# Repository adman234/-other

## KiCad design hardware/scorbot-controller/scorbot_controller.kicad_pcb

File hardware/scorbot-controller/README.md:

# Scorbot ER-4u ESP32 master board (KiCad)

KiCad project for the replacement controller: an ESP32 DevKit, six Pololu
DRV8874 carriers, a DROK mini 5 V buck module and two ADS1115 ADC
modules plug into a master board, and the robot's DD-50 cable plugs straight
into the board edge. The only SMD chip left for JLCPCB to place is the
TCA9555; everything else on the board is passives, LEDs and diodes.

**Status: v0.2, generated: schematic complete, PCB placed and autorouted (needs a human review before ordering).**

| File | What it is |
| --- | --- |
| `scorbot_controller.kicad_pro/.kicad_sch/.kicad_pcb` | The KiCad project (opens in KiCad 7, 8 or 9) |
| `lib/Scorbot.kicad_sym`, `lib/Scorbot.pretty/` | Custom parts: DevKit socket, DRV8874 carrier socket, DD-50 female R/A |
| `docs/schematic.pdf`, `docs/pcb_placement.png`, `docs/pcb_routed_F.png`, `docs/pcb_routed_B.png` | Previews (B side is mirrored) |
| `bom.csv` | Grouped BOM |
| `generator/design.py` | **Single source of truth**: every part, footprint, pin-to-net map and placement |
| `generate.sh` | Regenerates everything from `design.py`, then checks it |

## Regenerating

```sh
pip install kiutils cairosvg   # plus KiCad 7+ (kicad-cli and its pcbnew Python module)
# optional autorouting: Java 17+, xvfb-run and the Freerouting 1.9.0 jar
# (https://github.com/freerouting/freerouting/releases/tag/v1.9.0)
FREEROUTING_JAR=/path/freerouting-1.9.0.jar ./generate.sh
```

Routing takes about 3 minutes. `gen_route.py` retries up to `FREEROUTING_TRIES`
times (default 3) because Freerouting's result varies between runs, and it
keeps the run with the fewest unconnected items.

`generate.sh` writes the library, schematic, PCB and BOM, then:

- exports KiCad's own netlist from the schematic and checks it against
  `design.py` pin by pin (currently 354 connections, 0 mismatches);
- runs KiCad DRC on the board. Current result: 0 unconnected items, 0
  clearance or courtyard errors, and a few silkscreen and thermal-relief
  warnings. `lib_footprint_issues` only appears when the
  standard KiCad libraries aren't in the global library table.

Editing the `.kicad_sch` / `.kicad_pcb` by hand is fine once you take over
the design; just stop running the generator after that, or it overwrites your
changes.

## Must check before ordering boards

Blockers (the board is wrong or unbuildable until these are done):

1. **Pololu carrier pin order is a placeholder, and probably wrong.** The
   #4035 board is 0.6" x 0.7", which only fits 7 pins per side, but
   `CARRIER_ROWS` has 6 + 8. IMODE is most likely not broken out (the
   carrier pulls it to GND through 20 k), leaving 7 logic pins. Copy the
   real order and row spacing from Pololu's pinout drawing (or a carrier in
   hand) into `CARRIER_ROWS` / `CARRIER_ROW_SPACING`, then re-run
   `generate.sh`; it re-places and re-routes the board.
2. **DevKit row spacing.** `DEVKIT_ROW_SPACING = 25.4` mm. Measure your
   38-pin DevKitC between pin centres; clones vary.
3. **DD-50 footprint** is generated from KiCad's D-sub geometry (pitch
   2.77 x 2.84 mm, rows 1 and 3 aligned, D-shell hole spacing 61.11 mm).
   Print the board 1:1 and lay the connector on it, or check the drawing of
   the exact right-angle part you buy.
4. **JLC part numbers.** `fab/jlc_bom.csv` holds LCSC numbers from memory
   and search snapshots. Look each one up in JLCPCB's parts library (value,
   package, Basic vs Extended, stock) before ordering.

Check in KiCad / the JLC preview:

5. **Module pin orders**: the DROK buck socket (`BUCK_PINS`: IN+, IN-,
   OUT-, OUT+; the module's EN pin hangs off the end) and the ADS1115
   breakout (`ADS1115_PINS`, Adafruit #1085 order; other sellers differ).
6. **Autorouted copper.** Freerouting's result is DRC-clean but not pretty:
   long parallel runs across the middle, and motor/VM traces near the
   encoder lines. Look over the VM and MOT paths in particular.
7. **Copper weight.** VM carries up to the 5 A fuse current on 1.5 mm
   traces, and the motor outputs up to about 2.9 A (carrier limit) on
   0.8 mm. On 1 oz copper that is roughly a 20-25 C rise at those peaks.
   Order 2 oz copper, or widen VM/MOT in `netclasses.py` / `gen_route.py`.
8. **Part orientation in JLC's placement preview**: diode and LED
   polarity (D1, D3-D7) and pin 1 of U5. KiCad-to-JLC rotations sometimes
   need a 90/180 degree fix in `jlc_cpl.csv`.
9. **Screw terminal wire entry** (J2, J3, J7) should face the board edge.
   Check in KiCad's 3D viewer.
10. **Mechanical fit**: board is 185 x 128 mm with M3 holes in the
    corners; check the enclosure and that the DevKit's USB port and
    antenna end are reachable/clear.

## Ordering at JLCPCB

`generator/gen_fab.py` (run by `generate.sh`) writes `fab/`:

- `scorbot_controller_gerbers.zip`: upload as the PCB (2 layers, 1.6 mm,
  2 oz copper recommended).
- `jlc_bom.csv` and `jlc_cpl.csv`: upload for PCB Assembly, top side only.
  These list only the SMD parts JLC places. Everything else is
  hand-soldered: see the buy list in the plan doc.

## Design notes

- **DB50 pinout**: SCORBOT-ER 4u User Manual, Chapter 8 (identical to the
  ER III manual Table D-1). Pins 37-44 unused; pin 22 (gripper switch) has no
  connection in the arm. Motor +/- labels differ between manuals; firmware
  sets direction.
- **Encoders**: bare IR LEDs + phototransistors. 47 R per axis from 5 V for
  VLED (ER III reference value; check against the ER-4u's upgraded PC510
  encoders). P0/P1 have 4.7 k pull-ups to 3.3 V and 1 nF, straight into the
  ESP32 (no buffer); the PCNT glitch filter handles noise.
- **Power input, two options**: barrel jack J1 or screw terminal J2 (same
  nets; use one).
- **Fuse, two options**: fit EITHER the on-board mini blade holder F1
  (Keystone 3568, 5 A ATM fuse) OR the screw terminal J7 with an inline
  fuse holder wired across it. They are in parallel: two fuses in at once
  double the trip current, and a bare wire in J7 bypasses F1.
- **No reverse-polarity FET**: a reversed supply forward-biases the
  unidirectional SMBJ18A and blows the fuse.
- **E-stop**: no relay; the NC contacts sit in the VM line (J3), so they must
  be rated for total motor current. Logic stays powered.
- **Carrier current limit**: VREF is pulled to SLEEP (3.3 V) by 10 k on the
  carrier and CS has 2.49 k, giving about 2.9 A. R21-R26 (DNP) lower it.
- **Current sense**: two ADS1115 modules (0x48: CS1-4, 0x49: CS5, CS6 and
  VM/5.7). CS reads 1.12 V/A; use the ADS1115's +/-4.096 V range.
- Plan, firmware architecture and API: see the "Scorbot ER-4u ESP32
  Controller Plan" doc.

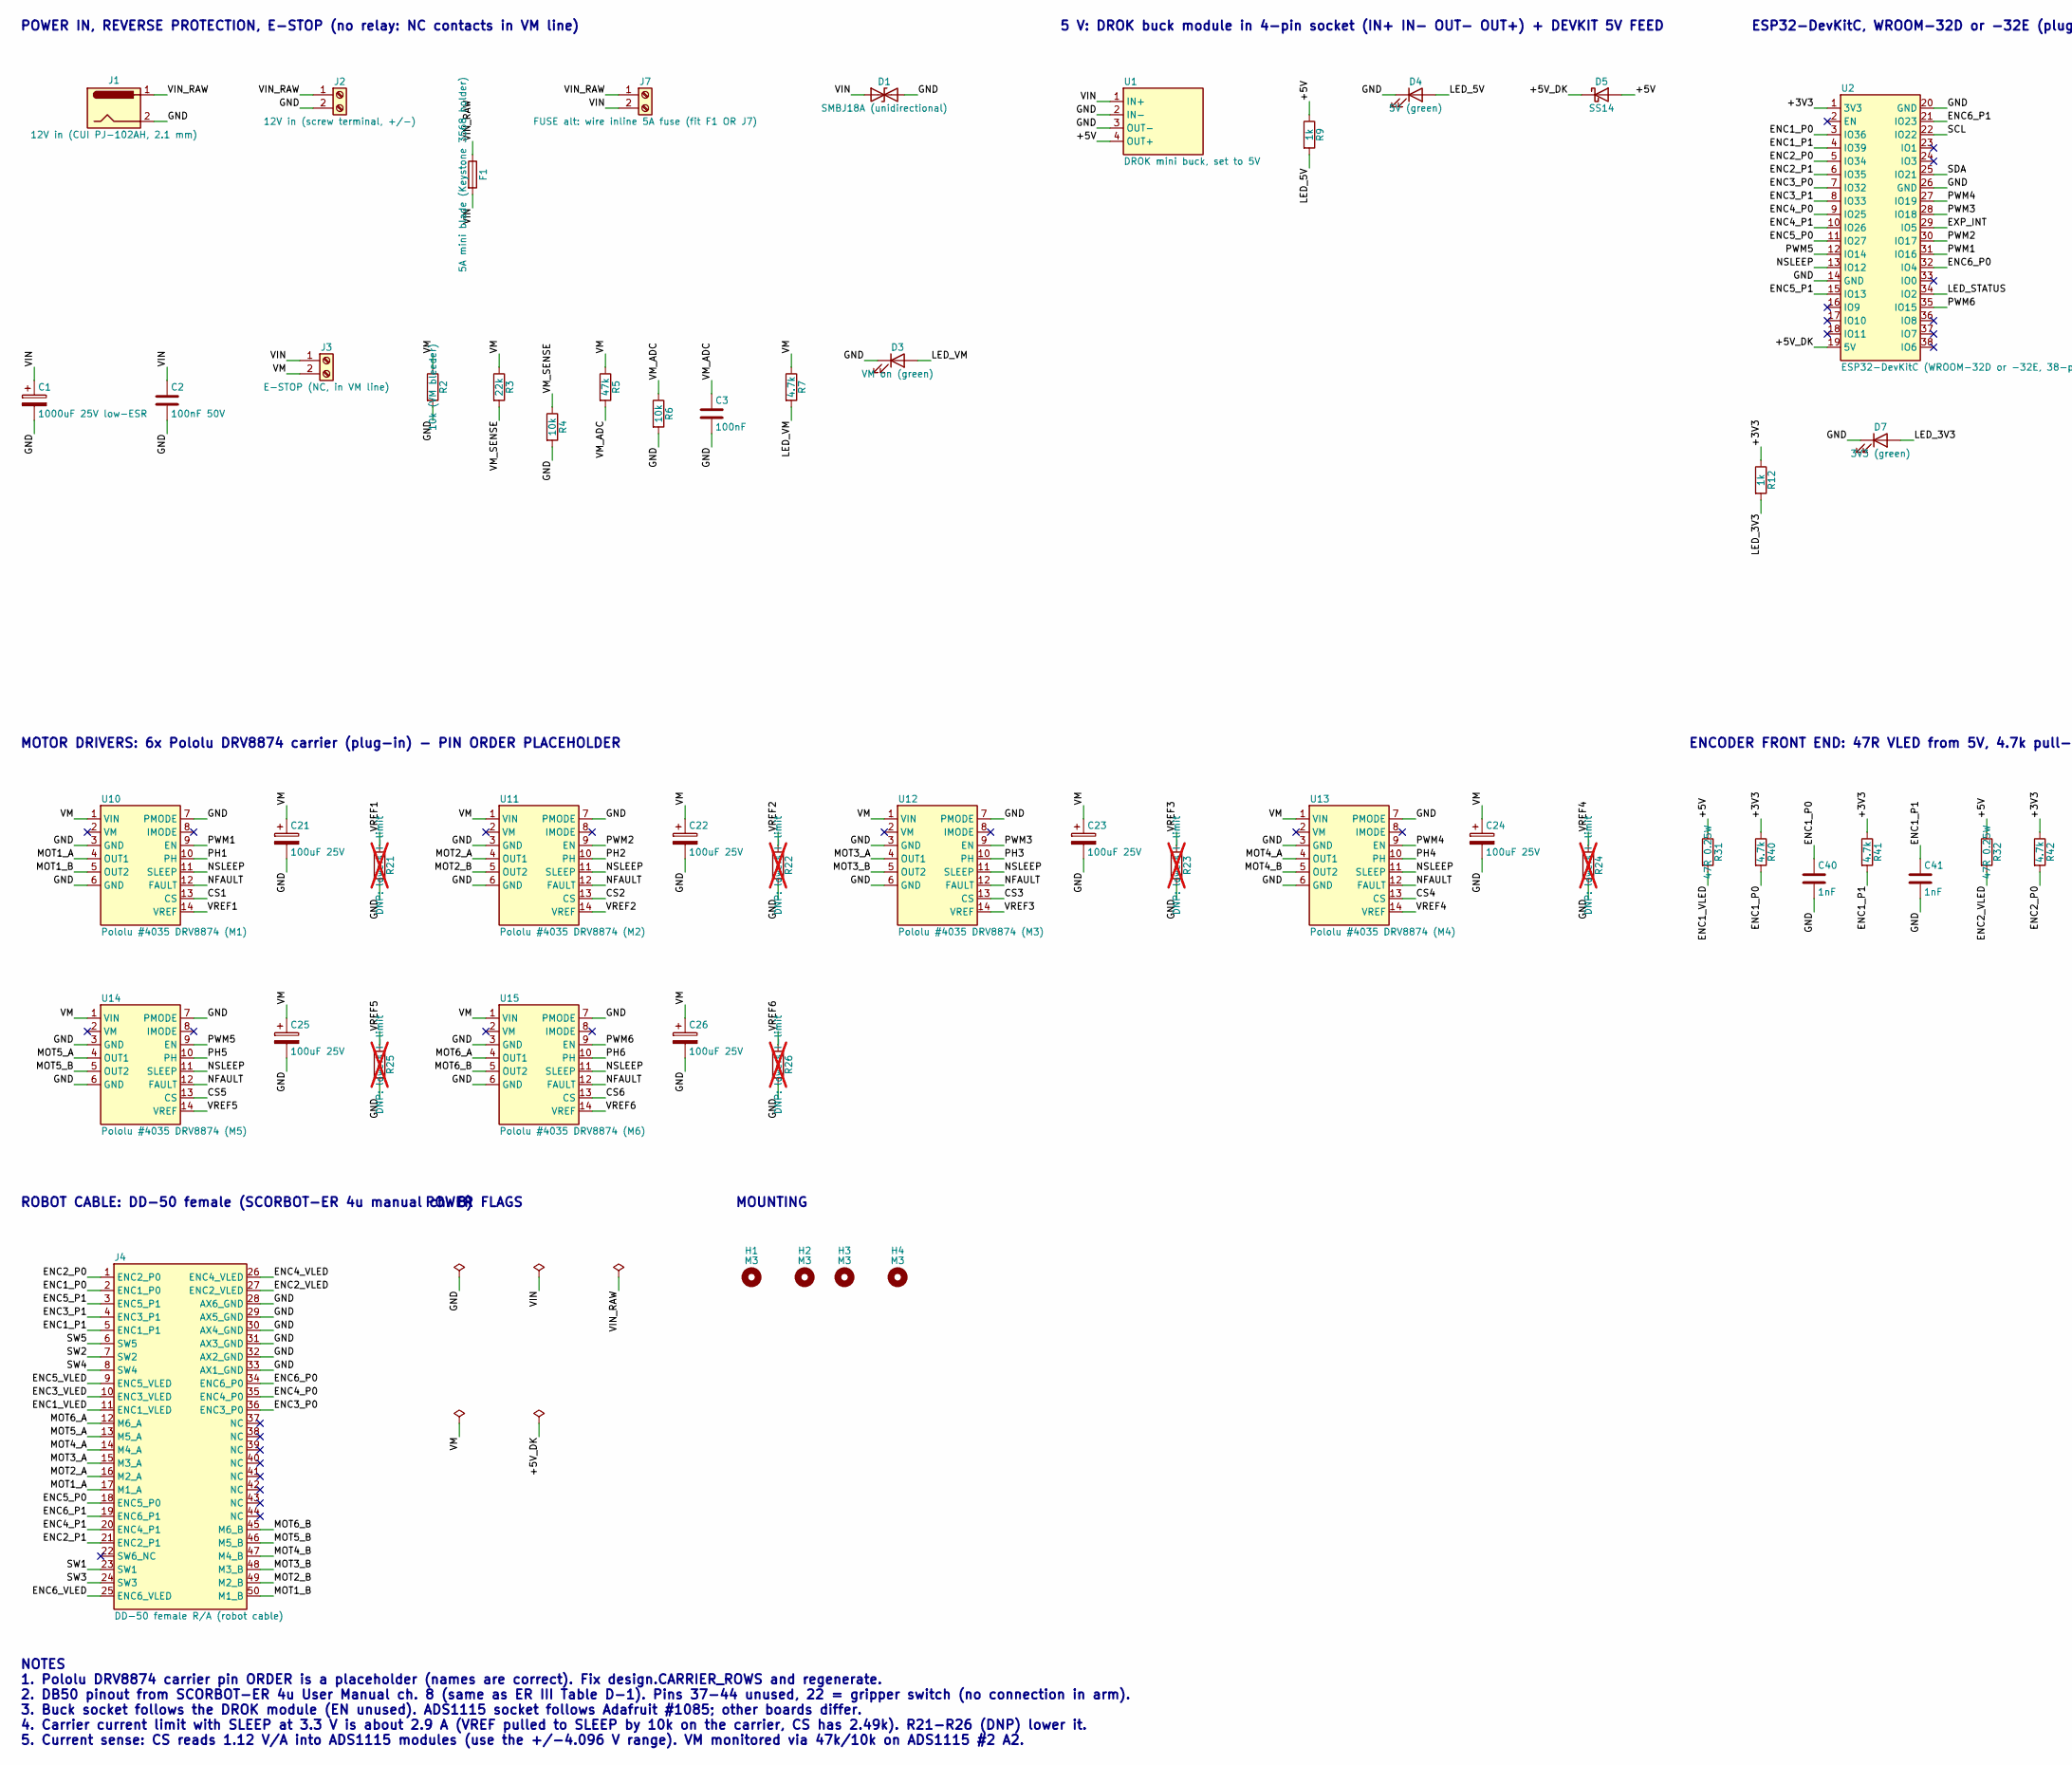
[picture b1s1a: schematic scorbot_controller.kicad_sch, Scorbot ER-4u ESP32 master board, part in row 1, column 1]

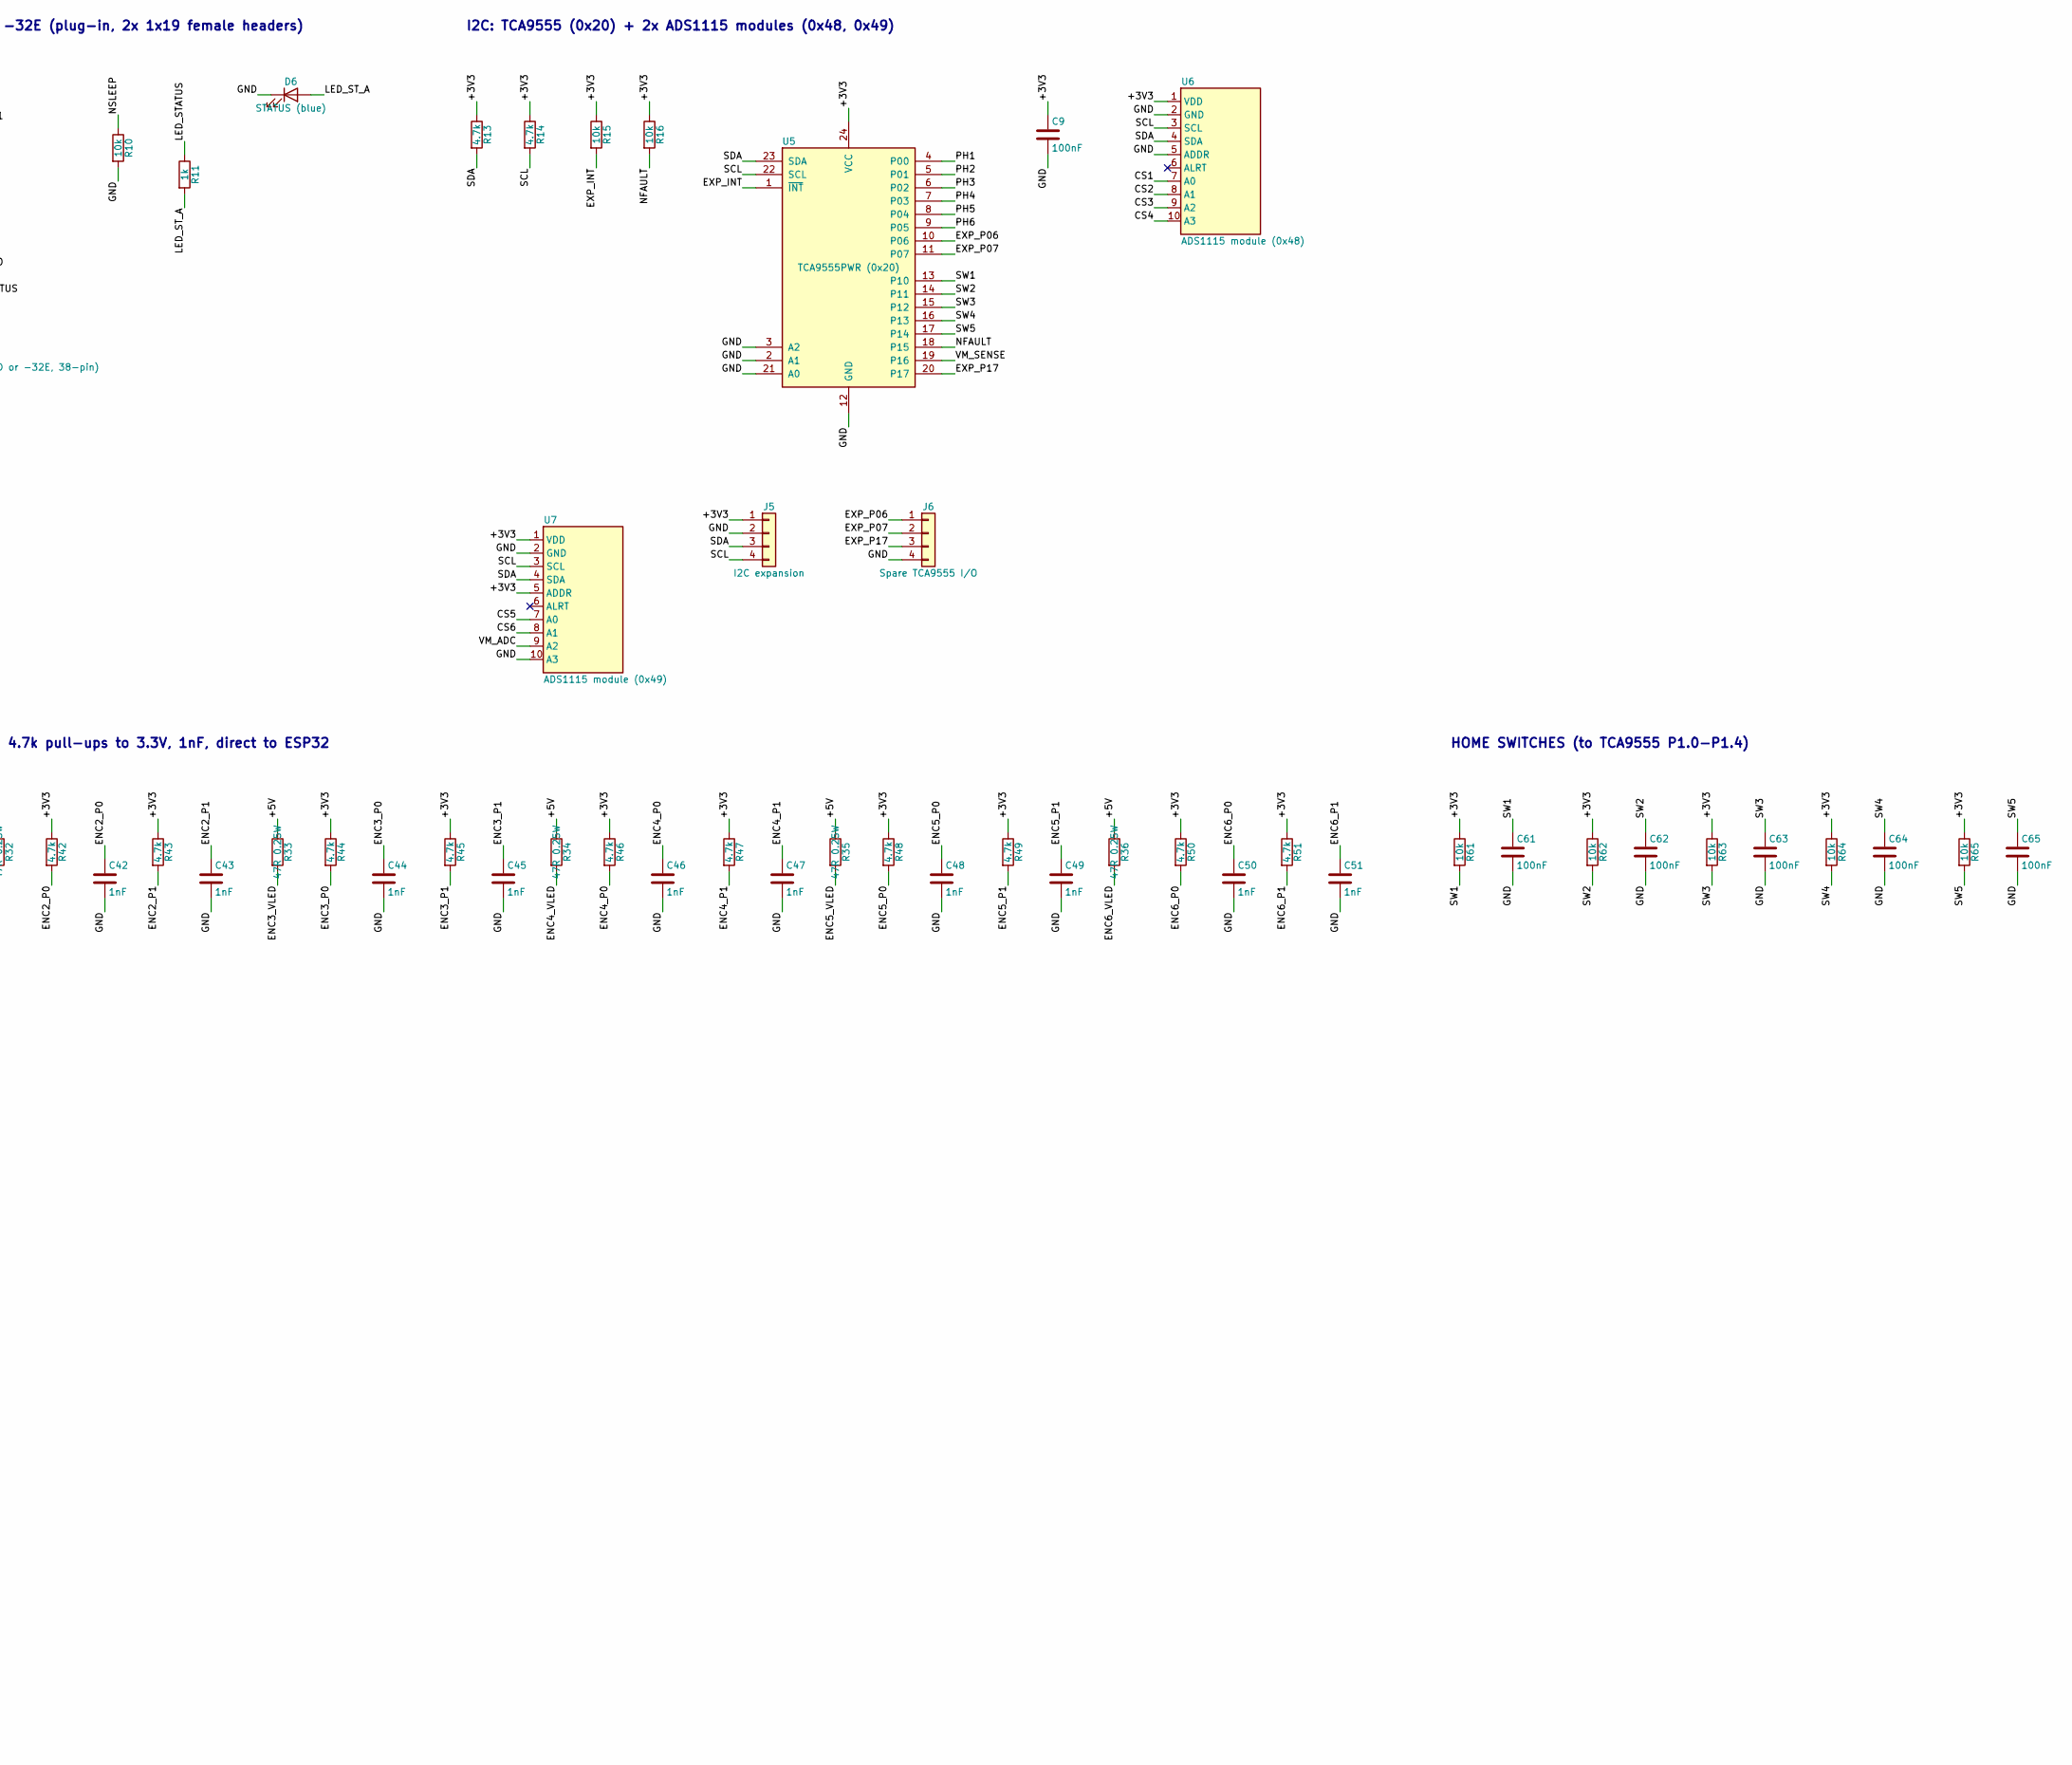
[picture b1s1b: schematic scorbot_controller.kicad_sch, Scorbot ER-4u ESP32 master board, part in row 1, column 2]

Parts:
C1: 1000uF 25V low-ESR; CP_Radial_D10.0mm_P5.00mm
C2: 100nF 50V; C_0805_2012Metric
C3, C9, C61, C62, C63, C64, C65: 100nF; C_0805_2012Metric
C21, C22, C23, C24, C25, C26: 100uF 25V; CP_Radial_D6.3mm_P2.50mm
C40, C41, C42, C43, C44, C45, C46, C47, C48, C49, C50, C51: 1nF; C_0805_2012Metric
D1: SMBJ18A (unidirectional); D_SMB
D3: VM on (green); LED_0805_2012Metric
D4: 5V (green); LED_0805_2012Metric
D5: SS14; D_SMA
D6: STATUS (blue); LED_0805_2012Metric
D7: 3V3 (green); LED_0805_2012Metric
F1: 5A mini blade (Keystone 3568 holder); Fuseholder_Blade_Mini_Keystone_3568
H1, H2, H3, H4: M3; MountingHole_3.2mm_M3
J1: 12V in (CUI PJ-102AH, 2.1 mm); BarrelJack_CUI_PJ-102AH_Horizontal
J2: 12V in (screw terminal, +/-); TerminalBlock_Phoenix_MKDS-1,5-2-5.08_1x02_P5.08mm_Horizont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
J3: E-STOP (NC, in VM line); TerminalBlock_Phoenix_MKDS-1,5-2-5.08_1x02_P5.08mm_Horizont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
J4: DD-50 female R/A (robot cable); DD50_Female_Horizontal_P2.77x2.84mm
J5: I2C expansion; PinHeader_1x04_P2.54mm_Vertical
J6: Spare TCA9555 I/O; PinHeader_1x04_P2.54mm_Vertical
J7: FUSE alt: wire inline 5A fuse (fit F1 OR J7); TerminalBlock_Phoenix_MKDS-1,5-2-5.08_1x02_P5.08mm_Horizont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
R2: 10k (VM bleeder); R_1206_3216Metric
R3: 22k; R_0805_2012Metric
R4, R6, R10, R15, R16, R61, R62, R63, R64, R65: 10k; R_0805_2012Metric
R5: 47k; R_0805_2012Metric
R7, R13, R14, R40, R41, R42, R43, R44, R45, R46, R47, R48, R49, R50, R51: 4.7k; R_0805_2012Metric
R9, R11, R12: 1k; R_0805_2012Metric
R21, R22, R23, R24, R25, R26: DNP: lowers I-limit; R_0805_2012Metric; not fitted
R31, R32, R33, R34, R35, R36: 47R 0.25W; R_1206_3216Metric
U1: DROK mini buck, set to 5V; Buck_Module_4pin_Socket
U2: ESP32-DevKitC (WROOM-32D or -32E, 38-pin); ESP32_DevKitC_V4_Socket
U5: TCA9555PWR (0x20); TSSOP-24_4.4x7.8mm_P0.65mm
U6: ADS1115 module (0x48); ADS1115_Module_Socket
U7: ADS1115 module (0x49); ADS1115_Module_Socket
U10: Pololu #4035 DRV8874 (M1); Pololu_DRV8874_Carrier_Socket
U11: Pololu #4035 DRV8874 (M2); Pololu_DRV8874_Carrier_Socket
U12: Pololu #4035 DRV8874 (M3); Pololu_DRV8874_Carrier_Socket
U13: Pololu #4035 DRV8874 (M4); Pololu_DRV8874_Carrier_Socket
U14: Pololu #4035 DRV8874 (M5); Pololu_DRV8874_Carrier_Socket
U15: Pololu #4035 DRV8874 (M6); Pololu_DRV8874_Carrier_Socket

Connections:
+3V3: C9.1, J5.1, R12.1, R13.1, R14.1, R15.1, R16.1, R40.1, R41.1, R42.1, R43.1, R44.1, R45.1, R46.1, R47.1, R48.1, R49.1, R50.1, R51.1, R61.1, R62.1, R63.1, R64.1, R65.1, U2.1 (3V3), U5.24 (VCC), U6.1 (VDD), U7.1 (VDD), U7.5 (ADDR)
+5V: D5.2 (A), R9.1, R31.1, R32.1, R33.1, R34.1, R35.1, R36.1, U1.4 (OUT+)
+5V_DK: D5.1 (K), U2.19 (5V)
CS1: U6.7 (A0), U10.13 (CS)
CS2: U6.8 (A1), U11.13 (CS)
CS3: U6.9 (A2), U12.13 (CS)
CS4: U6.10 (A3), U13.13 (CS)
CS5: U7.7 (A0), U14.13 (CS)
CS6: U7.8 (A1), U15.13 (CS)
ENC1_P0: C40.1, J4.2 (ENC1_P0), R40.2, U2.3 (IO36)
ENC1_P1: C41.1, J4.5 (ENC1_P1), R41.2, U2.4 (IO39)
ENC1_VLED: J4.11 (ENC1_VLED), R31.2
ENC2_P0: C42.1, J4.1 (ENC2_P0), R42.2, U2.5 (IO34)
ENC2_P1: C43.1, J4.21 (ENC2_P1), R43.2, U2.6 (IO35)
ENC2_VLED: J4.27 (ENC2_VLED), R32.2
ENC3_P0: C44.1, J4.36 (ENC3_P0), R44.2, U2.7 (IO32)
ENC3_P1: C45.1, J4.4 (ENC3_P1), R45.2, U2.8 (IO33)
ENC3_VLED: J4.10 (ENC3_VLED), R33.2
ENC4_P0: C46.1, J4.35 (ENC4_P0), R46.2, U2.9 (IO25)
ENC4_P1: C47.1, J4.20 (ENC4_P1), R47.2, U2.10 (IO26)
ENC4_VLED: J4.26 (ENC4_VLED), R34.2
ENC5_P0: C48.1, J4.18 (ENC5_P0), R48.2, U2.11 (IO27)
ENC5_P1: C49.1, J4.3 (ENC5_P1), R49.2, U2.15 (IO13)
ENC5_VLED: J4.9 (ENC5_VLED), R35.2
ENC6_P0: C50.1, J4.34 (ENC6_P0), R50.2, U2.32 (IO4)
ENC6_P1: C51.1, J4.19 (ENC6_P1), R51.2, U2.21 (IO23)
ENC6_VLED: J4.25 (ENC6_VLED), R36.2
EXP_INT: R15.2, U2.29 (IO5), U5.1 (~INT)
EXP_P06: J6.1, U5.10 (P06)
EXP_P07: J6.2, U5.11 (P07)
EXP_P17: J6.3, U5.20 (P17)
GND: C1.2, C2.2, C3.2, C9.2, C21.2, C22.2, C23.2, C24.2, C25.2, C26.2, C40.2, C41.2, C42.2, C43.2, C44.2, C45.2, C46.2, C47.2, C48.2, C49.2, C50.2, C51.2, C61.2, C62.2, C63.2, C64.2, C65.2, D1.2 (A2), D3.1 (K), D4.1 (K), D6.1 (K), D7.1 (K), J1.2, J2.2, J4.28 (AX6_GND), J4.29 (AX5_GND), J4.30 (AX4_GND), J4.31 (AX3_GND), J4.32 (AX2_GND), J4.33 (AX1_GND), J5.2, J6.4, R2.2, R4.2, R6.2, R10.2, R21.2, R22.2, R23.2, R24.2, R25.2, R26.2, U1.2 (IN-), U1.3 (OUT-), U2.14 (GND), U2.20 (GND), U2.26 (GND), U5.2 (A1), U5.3 (A2), U5.12 (GND), U5.21 (A0), U6.2 (GND), U6.5 (ADDR), U7.2 (GND), U7.10 (A3), U10.3 (GND), U10.6 (GND), U10.7 (PMODE), U11.3 (GND), U11.6 (GND), U11.7 (PMODE), U12.3 (GND), U12.6 (GND), U12.7 (PMODE), U13.3 (GND), U13.6 (GND), U13.7 (PMODE), U14.3 (GND), U14.6 (GND), U14.7 (PMODE), U15.3 (GND), U15.6 (GND), U15.7 (PMODE)
LED_3V3: D7.2 (A), R12.2
LED_5V: D4.2 (A), R9.2
LED_STATUS: R11.1, U2.34 (IO2)
LED_ST_A: D6.2 (A), R11.2
LED_VM: D3.2 (A), R7.2
MOT1_A: J4.17 (M1_A), U10.4 (OUT1)
MOT1_B: J4.50 (M1_B), U10.5 (OUT2)
MOT2_A: J4.16 (M2_A), U11.4 (OUT1)
MOT2_B: J4.49 (M2_B), U11.5 (OUT2)
MOT3_A: J4.15 (M3_A), U12.4 (OUT1)
MOT3_B: J4.48 (M3_B), U12.5 (OUT2)
MOT4_A: J4.14 (M4_A), U13.4 (OUT1)
MOT4_B: J4.47 (M4_B), U13.5 (OUT2)
MOT5_A: J4.13 (M5_A), U14.4 (OUT1)
MOT5_B: J4.46 (M5_B), U14.5 (OUT2)
MOT6_A: J4.12 (M6_A), U15.4 (OUT1)
MOT6_B: J4.45 (M6_B), U15.5 (OUT2)
NFAULT: R16.2, U5.18 (P15), U10.12 (FAULT), U11.12 (FAULT), U12.12 (FAULT), U13.12 (FAULT), U14.12 (FAULT), U15.12 (FAULT)
NSLEEP: R10.1, U2.13 (IO12), U10.11 (SLEEP), U11.11 (SLEEP), U12.11 (SLEEP), U13.11 (SLEEP), U14.11 (SLEEP), U15.11 (SLEEP)
PH1: U5.4 (P00), U10.10 (PH)
PH2: U5.5 (P01), U11.10 (PH)
PH3: U5.6 (P02), U12.10 (PH)
PH4: U5.7 (P03), U13.10 (PH)
PH5: U5.8 (P04), U14.10 (PH)
PH6: U5.9 (P05), U15.10 (PH)
PWM1: U2.31 (IO16), U10.9 (EN)
PWM2: U2.30 (IO17), U11.9 (EN)
PWM3: U2.28 (IO18), U12.9 (EN)
PWM4: U2.27 (IO19), U13.9 (EN)
PWM5: U2.12 (IO14), U14.9 (EN)
PWM6: U2.35 (IO15), U15.9 (EN)
SCL: J5.4, R14.2, U2.22 (IO22), U5.22 (SCL), U6.3 (SCL), U7.3 (SCL)
SDA: J5.3, R13.2, U2.25 (IO21), U5.23 (SDA), U6.4 (SDA), U7.4 (SDA)
SW1: C61.1, J4.23 (SW1), R61.2, U5.13 (P10)
SW2: C62.1, J4.7 (SW2), R62.2, U5.14 (P11)
SW3: C63.1, J4.24 (SW3), R63.2, U5.15 (P12)
SW4: C64.1, J4.8 (SW4), R64.2, U5.16 (P13)
SW5: C65.1, J4.6 (SW5), R65.2, U5.17 (P14)
VIN: C1.1, C2.1, D1.1 (A1), F1.2, J3.1, J7.2, U1.1 (IN+)
VIN_RAW: F1.1, J1.1, J2.1, J7.1
VM: C21.1, C22.1, C23.1, C24.1, C25.1, C26.1, J3.2, R2.1, R3.1, R5.1, R7.1, U10.1 (VIN), U11.1 (VIN), U12.1 (VIN), U13.1 (VIN), U14.1 (VIN), U15.1 (VIN)
VM_ADC: C3.1, R5.2, R6.1, U7.9 (A2)
VM_SENSE: R3.2, R4.1, U5.19 (P16)
VREF1: R21.1, U10.14 (VREF)
VREF2: R22.1, U11.14 (VREF)
VREF3: R23.1, U12.14 (VREF)
VREF4: R24.1, U13.14 (VREF)
VREF5: R25.1, U14.14 (VREF)
VREF6: R26.1, U15.14 (VREF)

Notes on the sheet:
POWER IN, REVERSE PROTECTION, E-STOP (no relay: NC contacts in VM line)
5 V: DROK buck module in 4-pin socket (IN+ IN- OUT- OUT+) + DEVKIT 5V FEED
ESP32-DevKitC, WROOM-32D or -32E (plug-in, 2x 1x19 female headers)
I2C: TCA9555 (0x20) + 2x ADS1115 modules (0x48, 0x49)
MOTOR DRIVERS: 6x Pololu DRV8874 carrier (plug-in) - PIN ORDER PLACEHOLDER
ENCODER FRONT END: 47R VLED from 5V, 4.7k pull-ups to 3.3V, 1nF, direct to ESP32
HOME SWITCHES (to TCA9555 P1.0-P1.4)
ROBOT CABLE: DD-50 female (SCORBOT-ER 4u manual ch. 8)
POWER FLAGS
MOUNTING
NOTES 1. Pololu DRV8874 carrier pin ORDER is a placeholder (names are correct). Fix design.CARRIER_ROWS and regenerate. 2. DB50 pinout from SCORBOT-ER 4u User Manual ch. 8 (same as ER III Table D-1). Pins 37-44 unused, 22 = gripper switch (no connection in arm). 3. Buck socket follows the DROK modu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

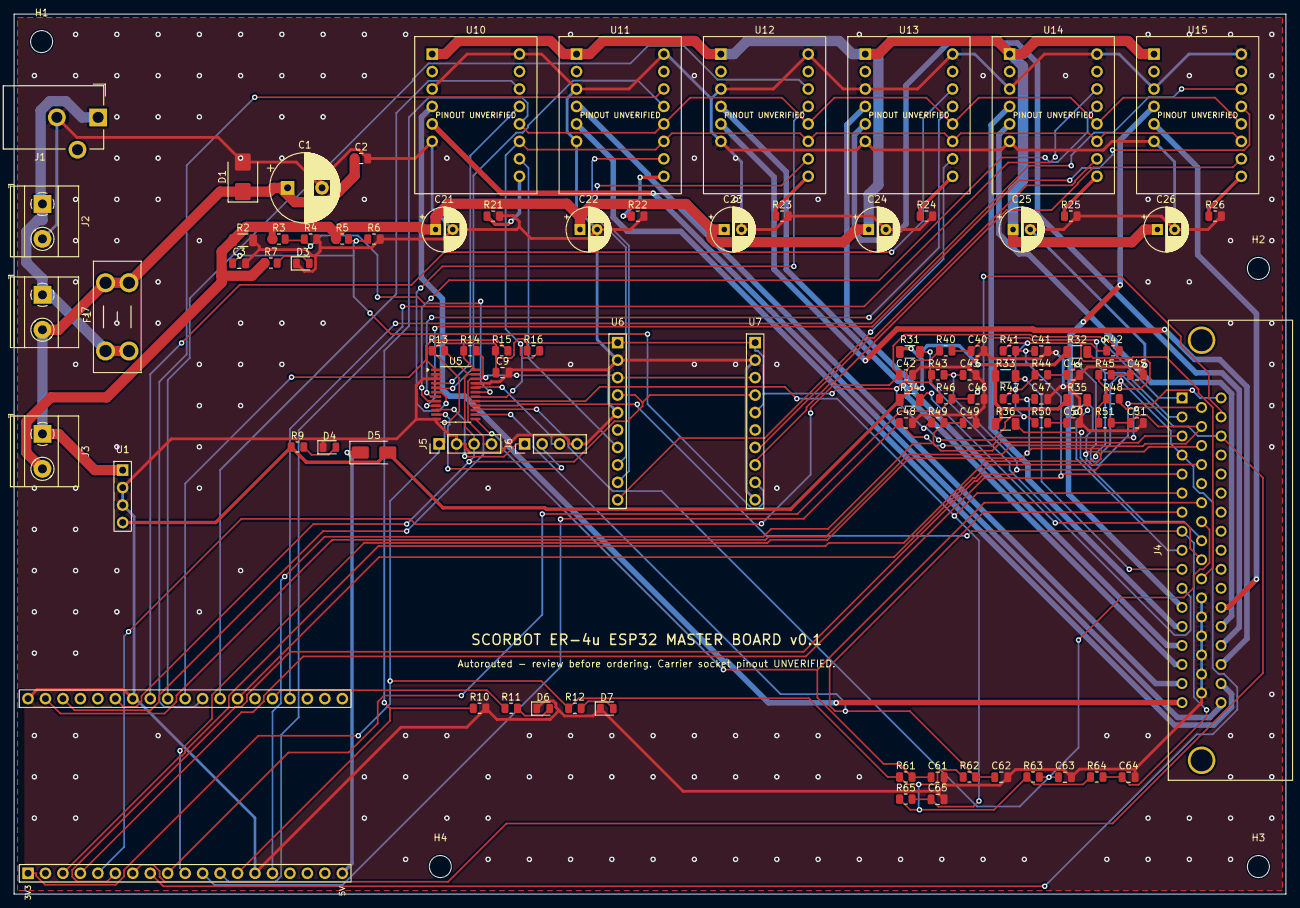
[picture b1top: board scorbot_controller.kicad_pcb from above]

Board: 2 copper layers, 185.0 x 128.0 mm, 99 parts (0 on the bottom side), 81 nets.

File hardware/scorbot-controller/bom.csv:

Qty,Value,Footprint,References,Populate
1,"12V in (CUI PJ-102AH, 2.1 mm)",Connector_BarrelJack:BarrelJack_CUI_PJ-102AH_Horizontal,J1,yes
1,"12V in (screw terminal, +/-)","TerminalBlock_Phoenix:TerminalBlock_Phoenix_MKDS-1,5-2-5.08_1x02_P5.08mm_Horizontal",J2,yes
1,5A mini blade (Keystone 3568 holder),Fuse:Fuseholder_Blade_Mini_Keystone_3568,F1,yes
1,FUSE alt: wire inline 5A fuse (fit F1 OR J7),"TerminalBlock_Phoenix:TerminalBlock_Phoenix_MKDS-1,5-2-5.08_1x02_P5.08mm_Horizontal",J7,yes
1,SMBJ18A (unidirectional),Diode_SMD:D_SMB,D1,yes
1,1000uF 25V low-ESR,Capacitor_THT:CP_Radial_D10.0mm_P5.00mm,C1,yes
1,100nF 50V,Capacitor_SMD:C_0805_2012Metric,C2,yes
1,"E-STOP (NC, in VM line)","TerminalBlock_Phoenix:TerminalBlock_Phoenix_MKDS-1,5-2-5.08_1x02_P5.08mm_Horizontal",J3,yes
1,10k (VM bleeder),Resistor_SMD:R_1206_3216Metric,R2,yes
1,22k,Resistor_SMD:R_0805_2012Metric,R3,yes
10,10k,Resistor_SMD:R_0805_2012Metric,R4 R6 R10 R15 R16 R61 R62 R63 R64 R65,yes
1,47k,Resistor_SMD:R_0805_2012Metric,R5,yes
7,100nF,Capacitor_SMD:C_0805_2012Metric,C3 C9 C61 C62 C63 C64 C65,yes
15,4.7k,Resistor_SMD:R_0805_2012Metric,R7 R13 R14 R40 R41 R42 R43 R44 R45 R46 R47 R48 R49 R50 R51,yes
1,VM on (green),LED_SMD:LED_0805_2012Metric,D3,yes
1,"DROK mini buck, set to 5V",Scorbot:Buck_Module_4pin_Socket,U1,yes
3,1k,Resistor_SMD:R_0805_2012Metric,R9 R11 R12,yes
1,5V (green),LED_SMD:LED_0805_2012Metric,D4,yes
1,SS14,Diode_SMD:D_SMA,D5,yes
1,"ESP32-DevKitC (WROOM-32D or -32E, 38-pin)",Scorbot:ESP32_DevKitC_V4_Socket,U2,yes
1,STATUS (blue),LED_SMD:LED_0805_2012Metric,D6,yes
1,3V3 (green),LED_SMD:LED_0805_2012Metric,D7,yes
1,TCA9555PWR (0x20),Package_SO:TSSOP-24_4.4x7.8mm_P0.65mm,U5,yes
1,ADS1115 module (0x48),Scorbot:ADS1115_Module_Socket,U6,yes
1,ADS1115 module (0x49),Scorbot:ADS1115_Module_Socket,U7,yes
1,I2C expansion,Connector_PinHeader_2.54mm:PinHeader_1x04_P2.54mm_Vertical,J5,yes
1,Spare TCA9555 I/O,Connector_PinHeader_2.54mm:PinHeader_1x04_P2.54mm_Vertical,J6,yes
1,Pololu #4035 DRV8874 (M1),Scorbot:Pololu_DRV8874_Carrier_Socket,U10,yes
6,100uF 25V,Capacitor_THT:CP_Radial_D6.3mm_P2.50mm,C21 C22 C23 C24 C25 C26,yes
6,DNP: lowers I-limit,Resistor_SMD:R_0805_2012Metric,R21 R22 R23 R24 R25 R26,DNP
1,Pololu #4035 DRV8874 (M2),Scorbot:Pololu_DRV8874_Carrier_Socket,U11,yes
1,Pololu #4035 DRV8874 (M3),Scorbot:Pololu_DRV8874_Carrier_Socket,U12,yes
1,Pololu #4035 DRV8874 (M4),Scorbot:Pololu_DRV8874_Carrier_Socket,U13,yes
1,Pololu #4035 DRV8874 (M5),Scorbot:Pololu_DRV8874_Carrier_Socket,U14,yes
1,Pololu #4035 DRV8874 (M6),Scorbot:Pololu_DRV8874_Carrier_Socket,U15,yes
6,47R 0.25W,Resistor_SMD:R_1206_3216Metric,R31 R32 R33 R34 R35 R36,yes
12,1nF,Capacitor_SMD:C_0805_2012Metric,C40 C41 C42 C43 C44 C45 C46 C47 C48 C49 C50 C51,yes
1,DD-50 female R/A (robot cable),Scorbot:DD50_Female_Horizontal_P2.77x2.84mm,J4,yes
4,M3,MountingHole:MountingHole_3.2mm_M3,H1 H2 H3 H4,yes
